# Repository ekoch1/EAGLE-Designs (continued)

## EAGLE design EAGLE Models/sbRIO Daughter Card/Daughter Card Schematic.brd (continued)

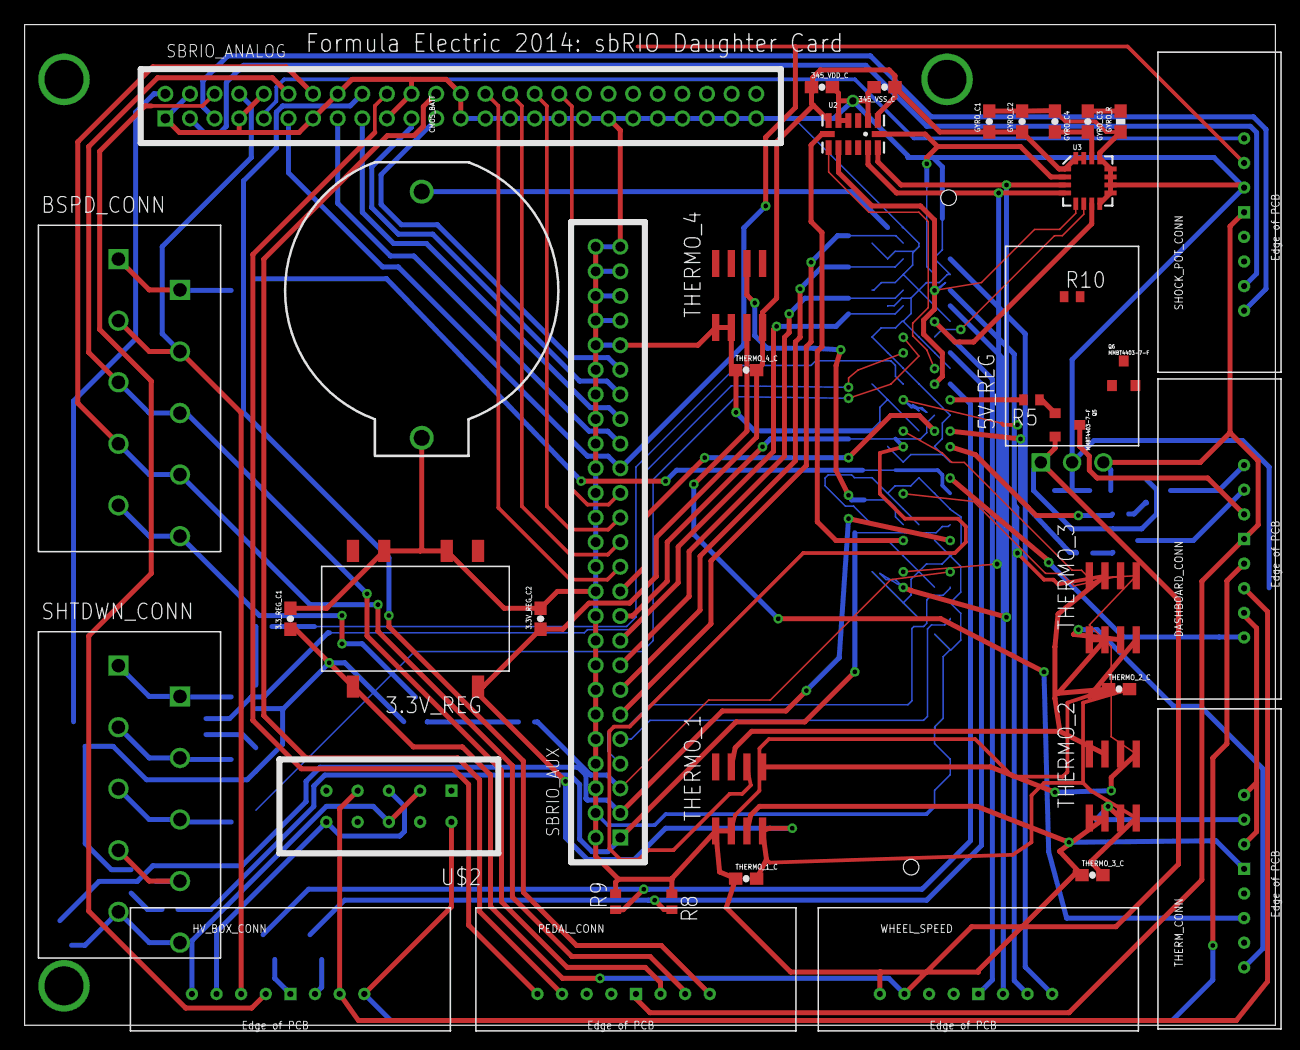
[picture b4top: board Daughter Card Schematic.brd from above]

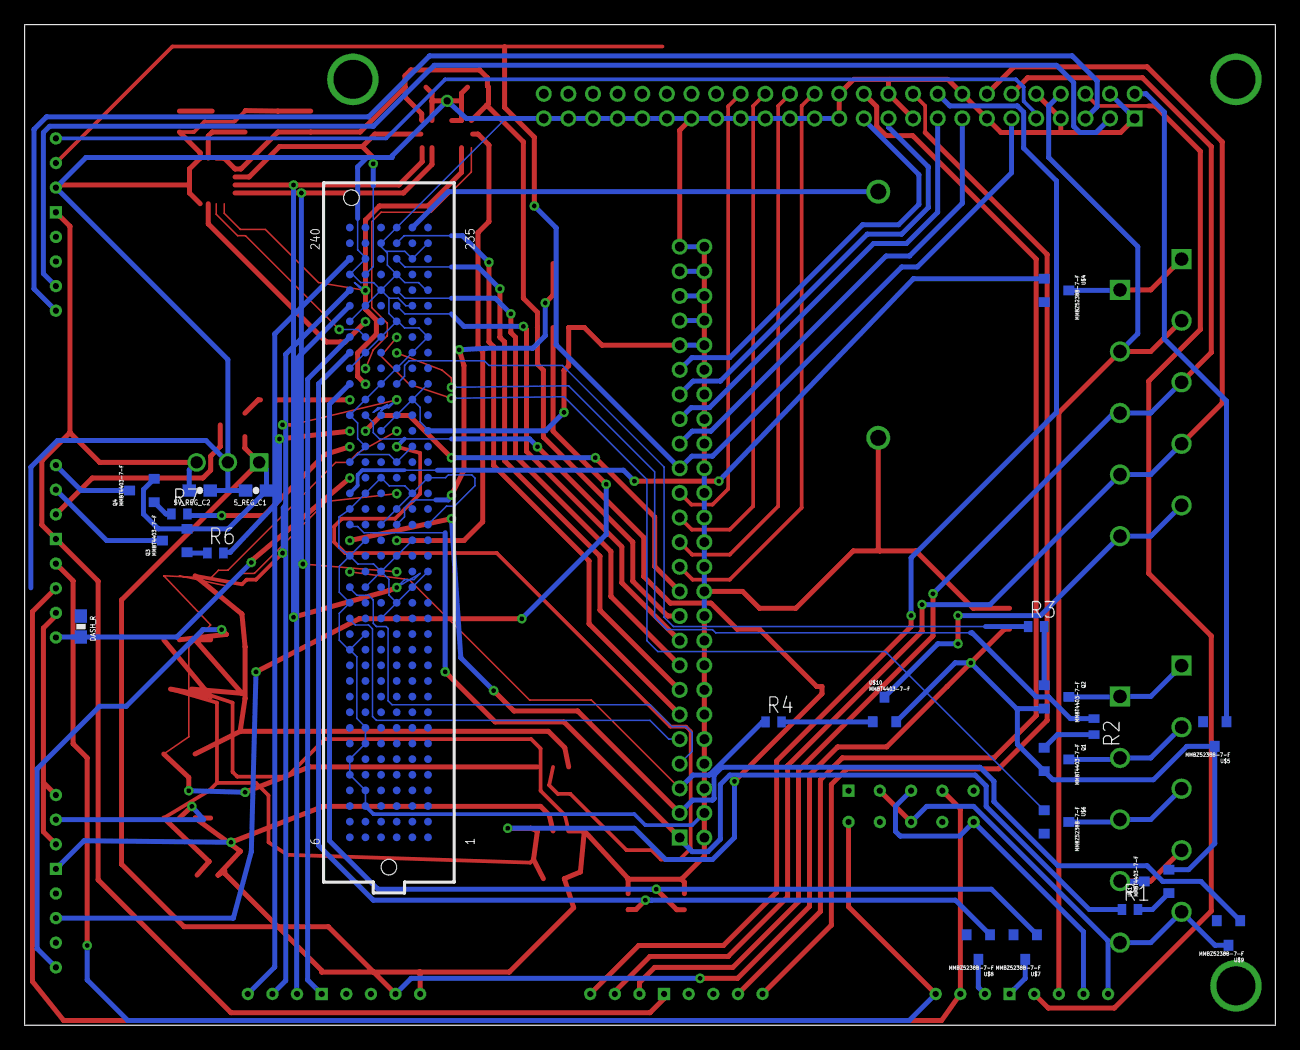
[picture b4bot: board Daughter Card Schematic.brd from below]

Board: 2 copper layers, 101.6 x 81.3 mm, 61 parts (22 on the bottom side), 95 nets.

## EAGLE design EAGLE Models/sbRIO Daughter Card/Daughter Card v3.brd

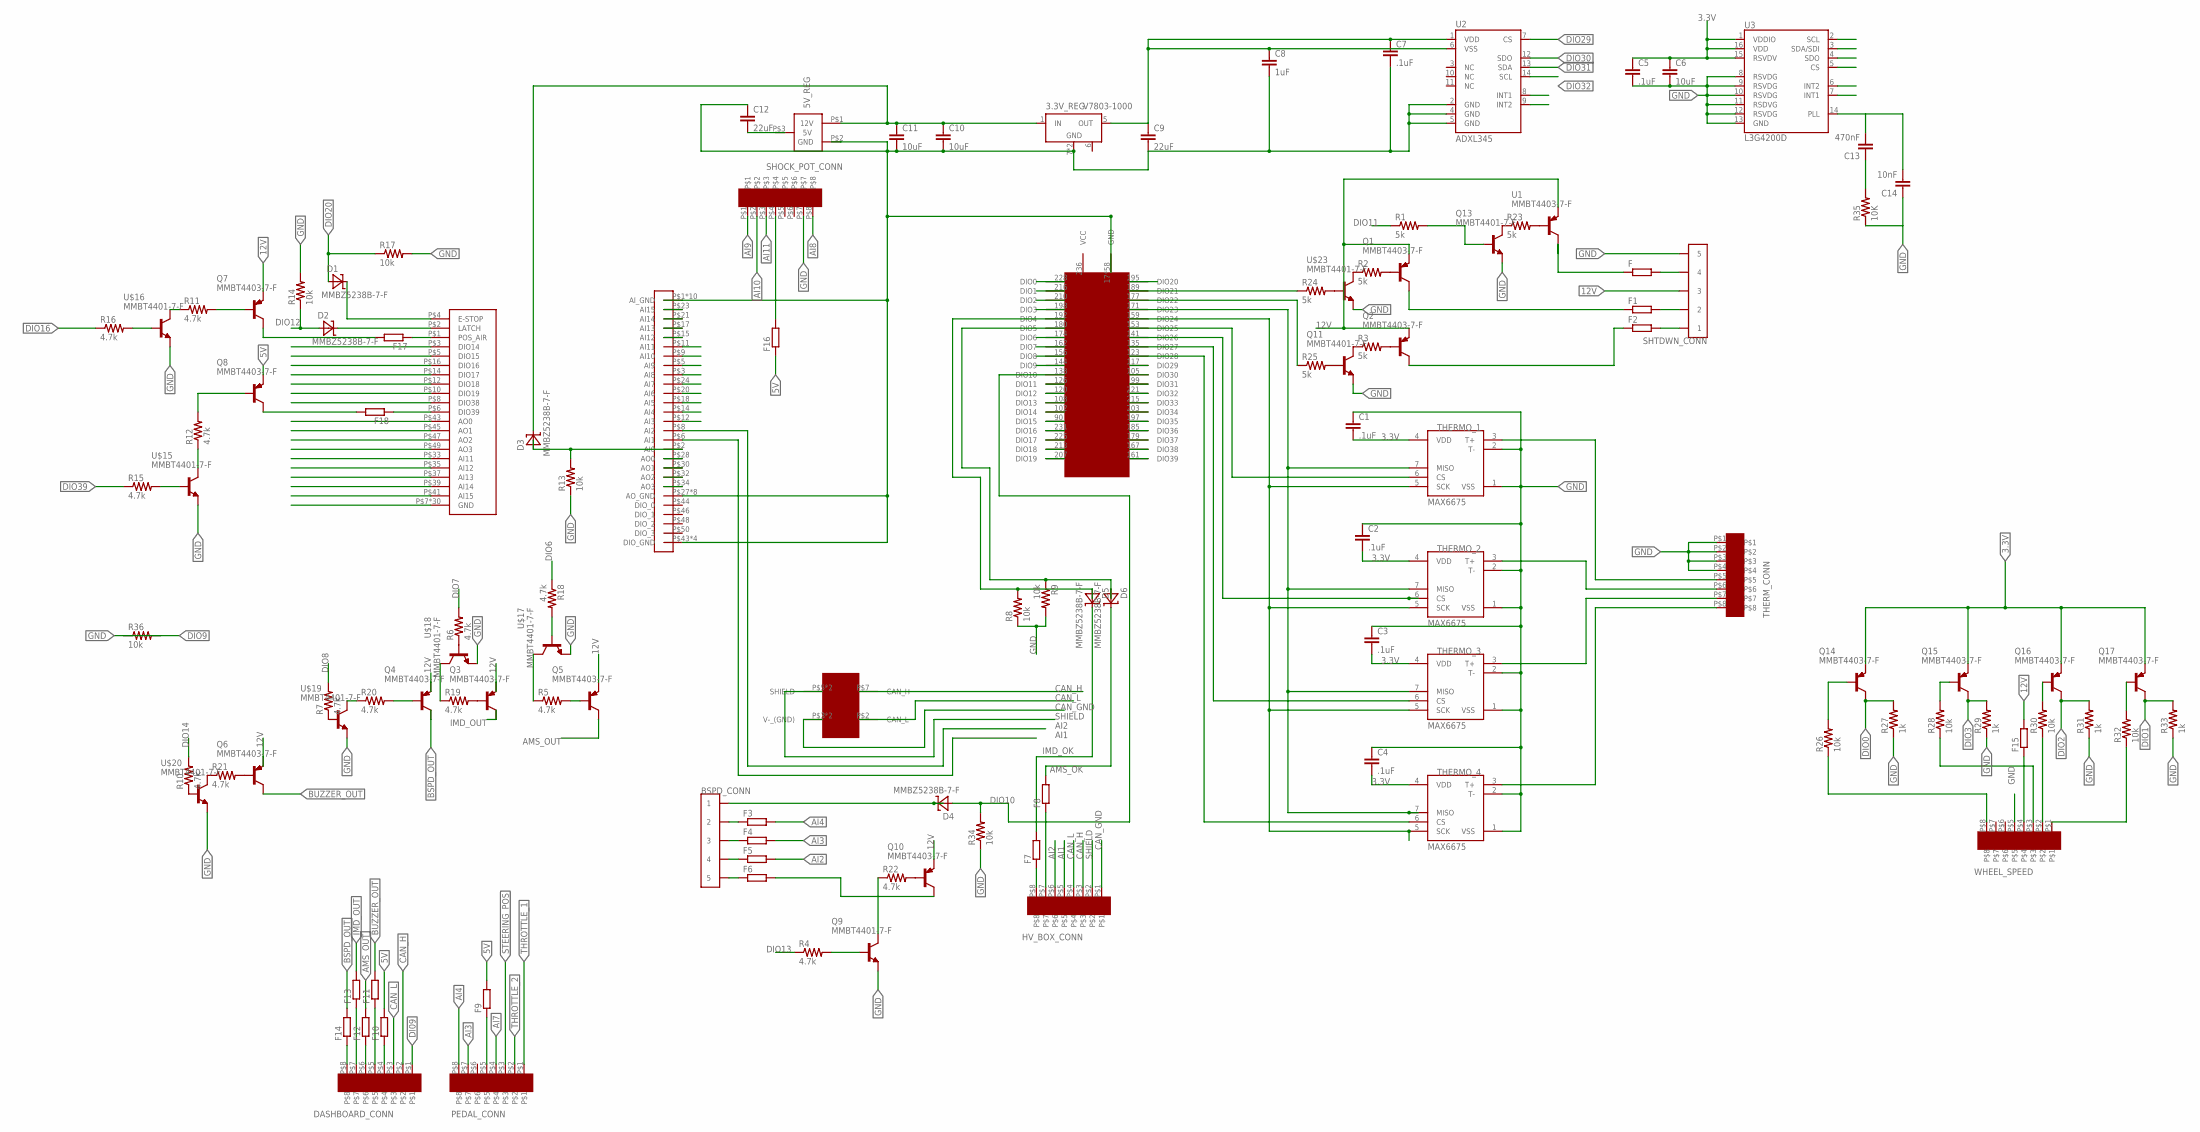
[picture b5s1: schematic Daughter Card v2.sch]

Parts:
3.3V_REG: V7803-1000; V78XX-1000
5V_REG: V78XX-1500; V78XX-1500R
BSPD_CONN: CONN_5; CONNECTOR_5
C1, C2, C3, C4, C5, C7: .1uF; 0603-CAP
C6, C10, C11: 10uF; 0603-CAP
C8: 1uF; 0603-CAP
C9, C12: 22uF; 0603-CAP
C13: 470nF; 0603-CAP
C14: 10nF; 0603-CAP
D1, D2, D3, D4, D5, D6: MMBZ5238B-7-F; SOT-23-3
DASHBOARD_CONN: EN3_PCB_8
F, F1, F2, F3, F4, F5, F6, F7, F8, F9, F10, F11, F12, F13, F14, F15, F16, F17, F18: R-EU_R0402; R0402
HV_BOX_CONN: EN3_PCB_8
PEDAL_CONN: EN3_PCB_8
Q1, Q2, Q3, Q4, Q5, Q6, Q7, Q8, Q10, Q14, Q15, Q16, Q17: MMBT4403-7-F; SOT-23-3
Q9, Q11, Q13: MMBT4401-7-F; SOT-23-3
R1, R2, R3, R23, R24, R25: 5k; R0402
R4, R5, R6, R7, R10, R11, R12, R15, R16, R18, R19, R20, R21, R22: 4.7k; R0402
R8, R9, R13, R14, R17, R26, R28, R30, R32, R34, R36: 10k; R0402
R27, R29, R31, R33: 1k; R0402
R35: 10K; 0603-RES
SBRIO_ANALOG: SBRIO_MIO; SBRIO_J502_J503
SBRIO_AUX: SBRIO_AUX; SBRIO_J502_J503
SHOCK_POT_CONN: EN3_PCB_8
SHTDWN_CONN: CONN_5; CONNECTOR_5
THERMO_1, THERMO_2, THERMO_3, THERMO_4: MAX6675; SO08
THERM_CONN: EN3_PCB_8
U1: MMBT4403-7-F; SOT-23-3
U2: ADXL345; LGA14
U3: L3G4200D; LGA16-4X4
U$2: SBRIO_W500; SBRIO_W
U$3: SBRIO_RMC; SEAM-40-XX.X-XX-06-X-A
U$15, U$16, U$17, U$18, U$19, U$20, U$23: MMBT4401-7-F; SOT-23-3
WHEEL_SPEED: EN3_PCB_8

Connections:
3.3V: 3.3V_REG.5 (OUT), C1.2, C2.2, C3.2, C4.2, C5.1, C6.1, C7.1, C8.1, C9.1, Q14.P$3 (E), Q15.P$3 (E), Q16.P$3 (E), Q17.P$3 (E), THERMO_1.4 (VDD), THERMO_2.4 (VDD), THERMO_3.4 (VDD), THERMO_4.4 (VDD), U2.1 (VDD), U2.6 (VSS), U3.1 (VDDIO), U3.15 (RSVDV), U3.16 (VDD)
AI1: HV_BOX_CONN.P$5, SBRIO_ANALOG.P$6 (AI1)
AI2: F5.2, HV_BOX_CONN.P$6, SBRIO_ANALOG.P$8 (AI2)
AI3: F4.2, PEDAL_CONN.P$7, SBRIO_ANALOG.P$12 (AI3)
AI4: F3.2, PEDAL_CONN.P$8, SBRIO_ANALOG.P$14 (AI4)
AI7: PEDAL_CONN.P$4, SBRIO_ANALOG.P$24 (AI7)
AI8: SBRIO_ANALOG.P$3 (AI8), SHOCK_POT_CONN.P$8
AI9: SBRIO_ANALOG.P$5 (AI9), SHOCK_POT_CONN.P$1
AI10: SBRIO_ANALOG.P$9 (AI10), SHOCK_POT_CONN.P$2
AI11: SBRIO_ANALOG.P$11 (AI11), SBRIO_AUX.P$33 (AI11), SHOCK_POT_CONN.P$3
AI12: SBRIO_ANALOG.P$15 (AI12), SBRIO_AUX.P$35 (AI12)
AI13: SBRIO_ANALOG.P$17 (AI13), SBRIO_AUX.P$37 (AI13)
AI15: SBRIO_ANALOG.P$23 (AI15), SBRIO_AUX.P$41 (AI15)
AMS_OK: D6.P$1 (C), F8.2
AMS_OUT: F12.2, Q5.P$1 (C)
AO0: SBRIO_ANALOG.P$28 (AO0), SBRIO_AUX.P$43 (AO0)
AO1: SBRIO_ANALOG.P$30 (AO1), SBRIO_AUX.P$45 (AO1)
AO2: SBRIO_ANALOG.P$32 (AO2), SBRIO_AUX.P$47 (AO2)
AO3: SBRIO_ANALOG.P$34 (AO3), SBRIO_AUX.P$49 (AO3)
BSPD_OUT: F14.2, Q4.P$1 (C)
BUZZER_OUT: F11.2, Q6.P$1 (C)
CAN_GND: HV_BOX_CONN.P$1, U$2.P$3 (V-_(GND)), U$2.P$6 (V-_(GND))
CAN_H: DASHBOARD_CONN.P$2, HV_BOX_CONN.P$3, U$2.P$7 (CAN_H)
CAN_L: DASHBOARD_CONN.P$3, HV_BOX_CONN.P$4, U$2.P$2 (CAN_L)
DI09: DASHBOARD_CONN.P$1
DIO0: Q14.P$1 (C), R27.2, U$3.228 (DIO0)
DIO1: Q17.P$1 (C), R33.2, U$3.216 (DIO1)
DIO2: Q16.P$1 (C), R31.2, U$3.210 (DIO2)
DIO3: Q15.P$1 (C), R29.2, U$3.198 (DIO3)
DIO6: R18.1, U$3.174 (DIO6)
DIO7: R6.2, U$3.162 (DIO7)
DIO8: R7.2, U$3.156 (DIO8)
DIO9: R36.2, U$3.144 (DIO9)
DIO10: D4.P$2 (A), R34.2, U$3.138 (DIO10)
DIO11: R1.1, U$3.126 (DIO11)
DIO12: D2.P$2 (A), R14.1, U$3.120 (DIO12)
DIO13: R4.1, U$3.108 (DIO13)
DIO14: R10.2, SBRIO_AUX.P$3 (DIO14), U$3.102 (DIO14)
DIO15: SBRIO_AUX.P$5 (DIO15), U$3.90 (DIO15)
DIO16: R16.1, SBRIO_AUX.P$16 (DIO16), U$3.231 (DIO16)
DIO17: SBRIO_AUX.P$14 (DIO17), U$3.225 (DIO17)
DIO18: SBRIO_AUX.P$12 (DIO18), U$3.213 (DIO18)
DIO19: SBRIO_AUX.P$10 (DIO19), U$3.207 (DIO19)
DIO20: D1.P$2 (A), R17.1, U$3.195 (DIO20)
DIO29: U2.7 (CS), U$3.117 (DIO29)
DIO30: U2.12 (SDO), U3.4 (SDO), U$3.105 (DIO30)
DIO31: U2.13 (SDA), U3.3 (SDA/SDI), U$3.99 (DIO31)
DIO32: U2.14 (SCL), U3.2 (SCL), U$3.221 (DIO32)
DIO33: U3.5 (CS), U$3.215 (DIO33)
DIO34: U3.7 (INT1), U$3.203 (DIO34)
DIO35: U3.6 (INT2), U$3.197 (DIO35)
DIO36: U2.8 (INT1), U$3.185 (DIO36)
DIO37: U2.9 (INT2), U$3.179 (DIO37)
DIO38: SBRIO_AUX.P$8 (DIO38), U$3.167 (DIO38)
DIO39: R15.1, U$3.161 (DIO39)
GND: 3.3V_REG.7 (GND), 3.3V_REG.9 (GND), 5V_REG.P$2 (GND), C1.1, C2.1, C3.1, C4.1, C5.2, C6.2, C7.2, C8.2, C9.2, C10.2, C11.2, C12.1, C14.1, Q9.P$3 (E), Q11.P$3 (E), Q13.P$3 (E), R8.1, R9.2, R13.1, R14.2, R17.2, R27.1, R29.1, R31.1, R33.1, R34.1, R35.1, R36.1, SBRIO_ANALOG.P$1 (AI_GND), SBRIO_ANALOG.P$4 (AI_GND), SBRIO_ANALOG.P$7 (AI_GND), SBRIO_ANALOG.P$10 (AI_GND), SBRIO_ANALOG.P$13 (AI_GND), SBRIO_ANALOG.P$16 (AI_GND), SBRIO_ANALOG.P$19 (AI_GND), SBRIO_ANALOG.P$22 (AI_GND), SBRIO_ANALOG.P$25 (AI_GND), SBRIO_ANALOG.P$26 (AI_GND), SBRIO_ANALOG.P$27 (AO_GND), SBRIO_ANALOG.P$29 (AO_GND), SBRIO_ANALOG.P$31 (AO_GND), SBRIO_ANALOG.P$33 (AO_GND), SBRIO_ANALOG.P$35 (AO_GND), SBRIO_ANALOG.P$37 (AO_GND), SBRIO_ANALOG.P$39 (AO_GND), SBRIO_ANALOG.P$41 (AO_GND), SBRIO_ANALOG.P$43 (DIO_GND), SBRIO_ANALOG.P$45 (DIO_GND), SBRIO_ANALOG.P$47 (DIO_GND), SBRIO_ANALOG.P$49 (DIO_GND), SBRIO_AUX.P$7 (GND), SBRIO_AUX.P$9 (GND), SBRIO_AUX.P$11 (GND), SBRIO_AUX.P$13 (GND), SBRIO_AUX.P$15 (GND), SBRIO_AUX.P$17 (GND), SBRIO_AUX.P$18 (GND), SBRIO_AUX.P$19 (GND), SBRIO_AUX.P$20 (GND), SBRIO_AUX.P$21 (GND), SBRIO_AUX.P$22 (GND), SBRIO_AUX.P$23 (GND), SBRIO_AUX.P$24 (GND), SBRIO_AUX.P$25 (GND), SBRIO_AUX.P$26 (GND), SBRIO_AUX.P$27 (GND), SBRIO_AUX.P$28 (GND), SBRIO_AUX.P$29 (GND), SBRIO_AUX.P$30 (GND), SBRIO_AUX.P$31 (GND), SBRIO_AUX.P$32 (GND), SBRIO_AUX.P$34 (GND), SBRIO_AUX.P$36 (GND), SBRIO_AUX.P$38 (GND), SBRIO_AUX.P$40 (GND), SBRIO_AUX.P$42 (GND), SBRIO_AUX.P$44 (GND), SBRIO_AUX.P$46 (GND), SBRIO_AUX.P$48 (GND), SBRIO_AUX.P$50 (GND), SHOCK_POT_CONN.P$7, SHTDWN_CONN.9 (5), SHTDWN_CONN.10 (5), THERMO_1.1 (VSS), THERMO_1.2 (T-), THERMO_2.1 (VSS), THERMO_2.2 (T-), THERMO_3.1 (VSS), THERMO_3.2 (T-), THERMO_4.1 (VSS), THERMO_4.2 (T-), THERM_CONN.P$1, THERM_CONN.P$2, THERM_CONN.P$3, THERM_CONN.P$4, U2.2 (GND), U2.4 (GND), U2.5 (GND), U3.8 (RSVDG), U3.9 (RSVDG), U3.10 (RSVDG), U3.11 (RSDVG), U3.12 (RSVDG), U3.13 (GND), U$3.17 (GND), U$3.237 (GND), U$15.P$3 (E), U$16.P$3 (E), U$17.P$3 (E), U$18.P$3 (E), U$19.P$3 (E), U$20.P$3 (E), U$23.P$3 (E), WHEEL_SPEED.P$5
IMD_OK: D5.P$1 (C), F7.2
IMD_OUT: F13.2, Q3.P$1 (C)
unnamed: D2.P$1 (C), SBRIO_AUX.P$2 (LATCH)
unnamed: D1.P$1 (C), SBRIO_AUX.P$4 (E-STOP)
unnamed: R32.1, WHEEL_SPEED.P$1
unnamed: D3.P$2 (A), R13.2, SBRIO_ANALOG.P$2 (AI0)
unnamed: Q6.P$2 (B), R21.2
unnamed: Q16.P$2 (B), R30.2
unnamed: F1.1, Q1.P$1 (C)
unnamed: F2.1, Q2.P$1 (C)
unnamed: R28.1, WHEEL_SPEED.P$3
unnamed: R26.1, WHEEL_SPEED.P$8
unnamed: R24.1, U$3.189 (DIO21)
unnamed: R25.1, U$3.177 (DIO22)
unnamed: F8.1, HV_BOX_CONN.P$7
unnamed: F7.1, HV_BOX_CONN.P$8
unnamed: D5.P$2 (A), R8.2, U$3.192 (DIO4)
unnamed: D6.P$2 (A), R9.1, U$3.180 (DIO5)
unnamed: THERMO_1.7 (MISO), THERMO_2.7 (MISO), THERMO_3.7 (MISO), THERMO_4.7 (MISO), U$3.171 (DIO23)
unnamed: THERMO_1.5 (SCK), THERMO_2.5 (SCK), THERMO_3.5 (SCK), THERMO_4.5 (SCK), U$3.159 (DIO24)
unnamed: F16.2, SHOCK_POT_CONN.P$4
unnamed: F15.1, WHEEL_SPEED.P$4
unnamed: F9.1, PEDAL_CONN.P$5
unnamed: DASHBOARD_CONN.P$4, F10.1
unnamed: DASHBOARD_CONN.P$5, F11.1
unnamed: THERMO_1.6 (CS), U$3.153 (DIO25)
unnamed: THERMO_2.6 (CS), U$3.141 (DIO26)
unnamed: THERMO_3.6 (CS), U$3.135 (DIO27)
unnamed: THERMO_4.6 (CS), U$3.123 (DIO28)
unnamed: THERMO_1.3 (T+), THERM_CONN.P$5
unnamed: THERMO_2.3 (T+), THERM_CONN.P$6
unnamed: THERMO_3.3 (T+), THERM_CONN.P$7
unnamed: THERMO_4.3 (T+), THERM_CONN.P$8
unnamed: DASHBOARD_CONN.P$6, F12.1
unnamed: DASHBOARD_CONN.P$7, F13.1
unnamed: DASHBOARD_CONN.P$8, F14.1
unnamed: F.2, SHTDWN_CONN.7 (4), SHTDWN_CONN.8 (4)
unnamed: C13.2, C14.2, U3.14 (PLL)
unnamed: C13.1, R35.2
unnamed: F1.2, SHTDWN_CONN.3 (2), SHTDWN_CONN.4 (2)
unnamed: F2.2, SHTDWN_CONN.1, SHTDWN_CONN.2 (1)
unnamed: BSPD_CONN.9 (5), BSPD_CONN.10 (5), F6.1
unnamed: BSPD_CONN.1, BSPD_CONN.2 (1), D4.P$1 (C)
unnamed: BSPD_CONN.7 (4), BSPD_CONN.8 (4), F5.1
unnamed: F.1, U1.P$1 (C)
unnamed: F6.2, Q10.P$1 (C)
unnamed: R23.2, U1.P$2 (B)
unnamed: Q1.P$2 (B), R2.2
unnamed: Q2.P$2 (B), R3.2
unnamed: Q10.P$2 (B), R22.2
unnamed: Q5.P$2 (B), R5.2
unnamed: Q3.P$2 (B), R19.2
unnamed: BSPD_CONN.5 (3), BSPD_CONN.6 (3), F4.1
unnamed: BSPD_CONN.3 (2), BSPD_CONN.4 (2), F3.1
unnamed: Q7.P$2 (B), R11.2
unnamed: F17.1, SBRIO_AUX.P$1 (POS_AIR)
unnamed: F17.2, Q7.P$1 (C)
unnamed: F18.2, Q8.P$1 (C)
unnamed: Q8.P$2 (B), R12.2
unnamed: F18.1, SBRIO_AUX.P$6 (DIO39)
unnamed: R15.2, U$15.P$2 (B)
unnamed: R12.1, U$15.P$1 (C)
unnamed: R16.2, U$16.P$2 (B)
unnamed: R11.1, U$16.P$1 (C)
unnamed: R5.1, U$17.P$1 (C)
unnamed: R18.2, U$17.P$2 (B)
unnamed: R19.1, U$18.P$1 (C)
unnamed: R6.1, U$18.P$2 (B)
unnamed: Q4.P$2 (B), R20.2
unnamed: R20.1, U$19.P$1 (C)
unnamed: R7.1, U$19.P$2 (B)
unnamed: R21.1, U$20.P$1 (C)
unnamed: R10.1, U$20.P$2 (B)
unnamed: Q9.P$1 (C), R22.1
unnamed: Q9.P$2 (B), R4.2
unnamed: Q13.P$1 (C), R23.1
unnamed: Q13.P$2 (B), R1.2
unnamed: R2.1, U$23.P$1 (C)
unnamed: Q11.P$1 (C), R3.1
unnamed: R24.2, U$23.P$2 (B)
unnamed: Q11.P$2 (B), R25.2
unnamed: Q14.P$2 (B), R26.2
unnamed: Q15.P$2 (B), R28.2
unnamed: R30.1, WHEEL_SPEED.P$2
unnamed: Q17.P$2 (B), R32.2
SHIELD: HV_BOX_CONN.P$2, U$2.P$5 (SHIELD), U$2.P$10 (SHIELD)
STEERING_POS: PEDAL_CONN.P$3, SBRIO_ANALOG.P$21 (AI14), SBRIO_AUX.P$39 (AI14)
THROTTLE_1: PEDAL_CONN.P$1, SBRIO_ANALOG.P$18 (AI5)
THROTTLE_2: PEDAL_CONN.P$2, SBRIO_ANALOG.P$20 (AI6)
VCC: U$3.236 (VCC)

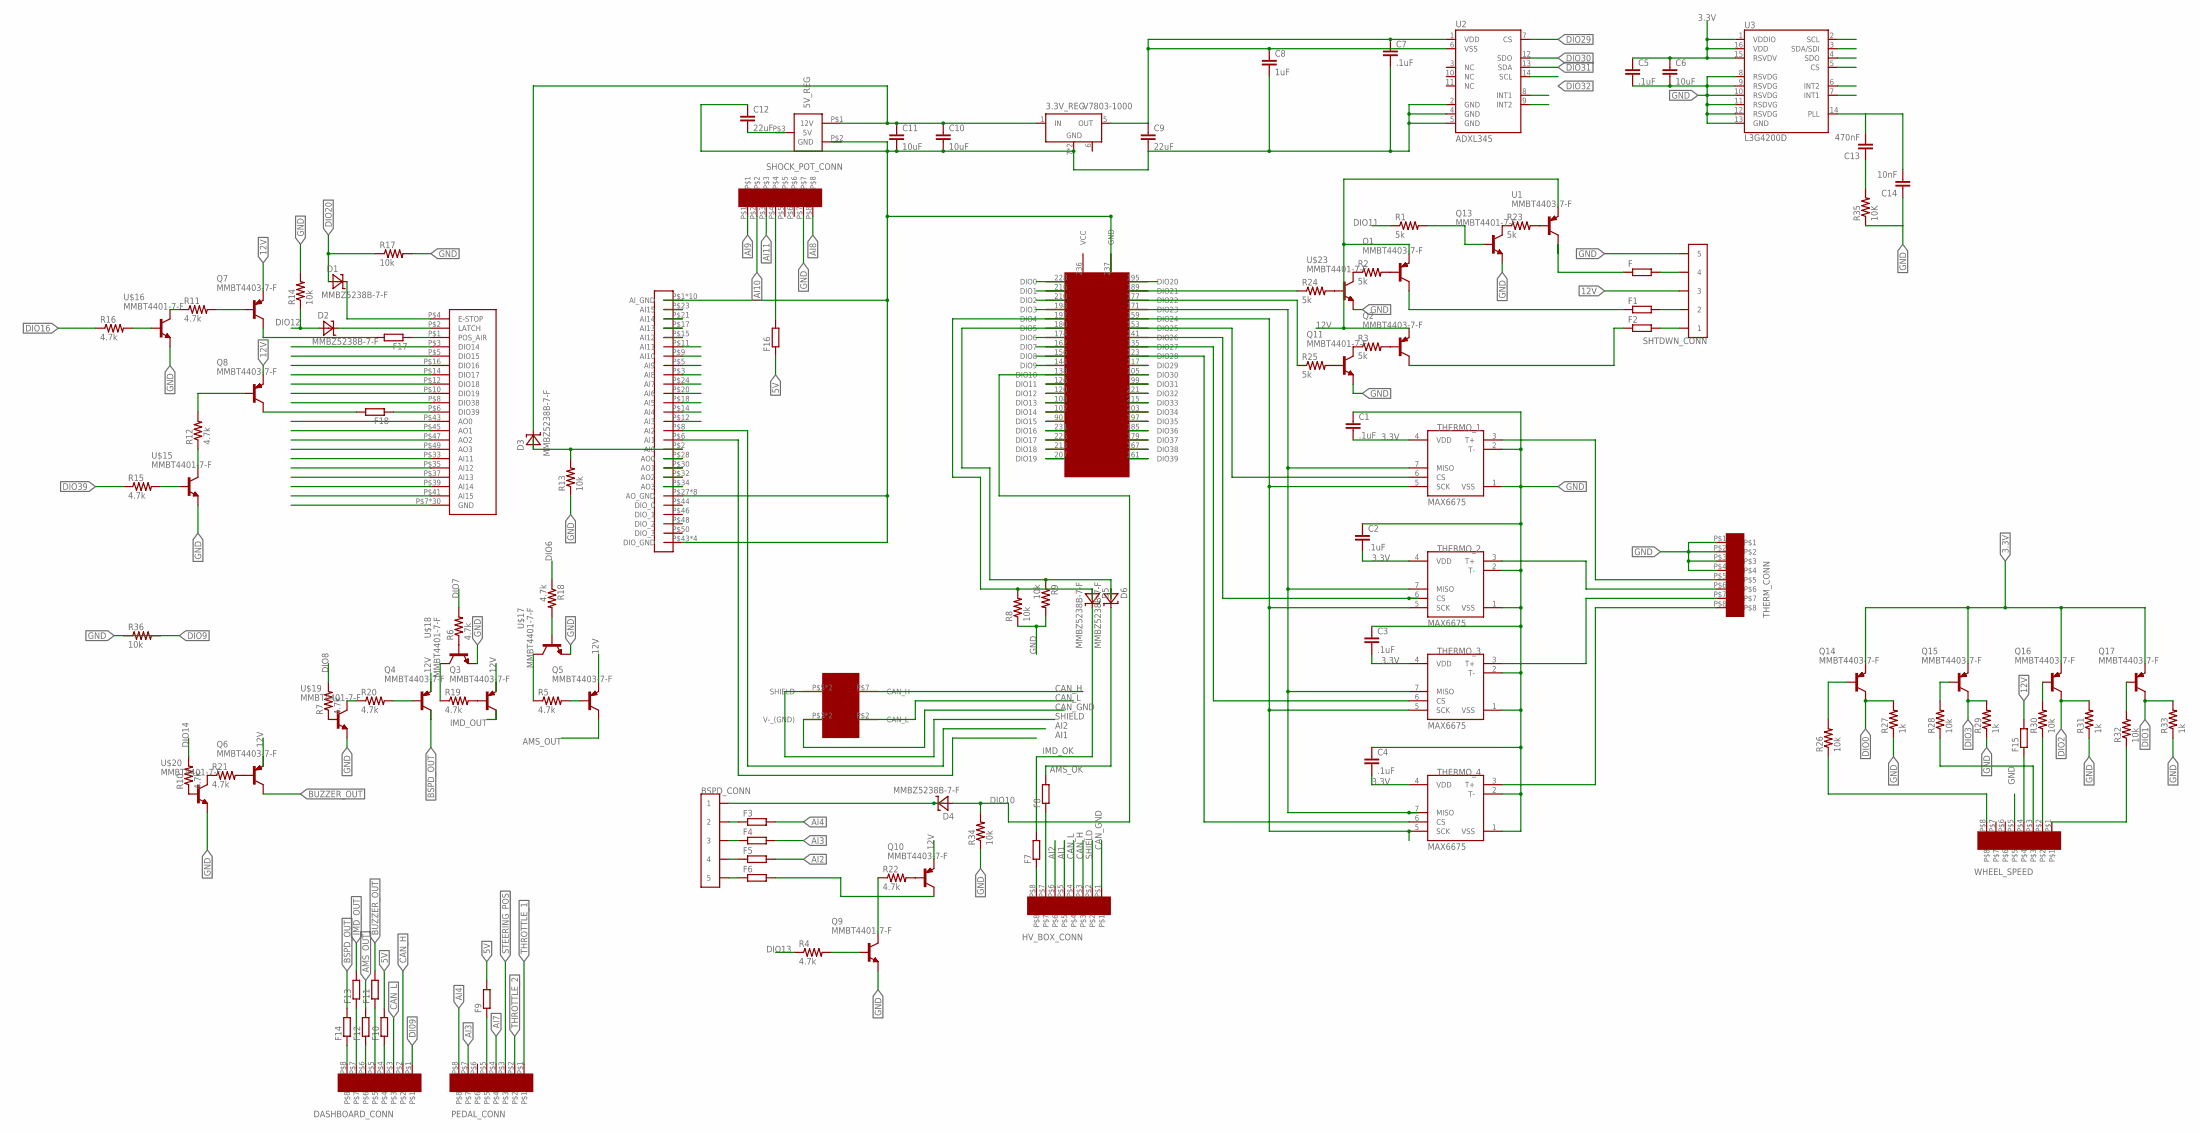
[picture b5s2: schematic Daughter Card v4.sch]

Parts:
3.3V_REG: V7803-1000; V78XX-1000
5V_REG: V78XX-1500; V78XX-1500R
BSPD_CONN: CONN_5; CONNECTOR_5
C1, C2, C3, C4, C5, C7: .1uF; 0603-CAP
C6, C10, C11: 10uF; 0603-CAP
C8: 1uF; 0603-CAP
C9, C12: 22uF; 0603-CAP
C13: 470nF; 0603-CAP
C14: 10nF; 0603-CAP
D1, D2, D3, D4, D5, D6: MMBZ5238B-7-F; SOT-23-3
DASHBOARD_CONN: EN3_PCB_8
F, F1, F2, F3, F4, F5, F6, F7, F8, F9, F10, F11, F12, F13, F14, F15, F16, F17, F18: R-EU_R0402; R0402
HV_BOX_CONN: EN3_PCB_8
PEDAL_CONN: EN3_PCB_8
Q1, Q2, Q3, Q4, Q5, Q6, Q7, Q8, Q10, Q14, Q15, Q16, Q17: MMBT4403-7-F; SOT-23-3
Q9, Q11, Q13: MMBT4401-7-F; SOT-23-3
R1, R2, R3, R23, R24, R25: 5k; R0402
R4, R5, R6, R7, R10, R11, R12, R15, R16, R18, R19, R20, R21, R22: 4.7k; R0402
R8, R9, R13, R14, R17, R26, R28, R30, R32, R34, R36: 10k; R0402
R27, R29, R31, R33: 1k; R0402
R35: 10K; 0603-RES
SBRIO_ANALOG: SBRIO_MIO; SBRIO_J502_J503
SBRIO_AUX: SBRIO_AUX; SBRIO_J502_J503
SHOCK_POT_CONN: EN3_PCB_8
SHTDWN_CONN: CONN_5; CONNECTOR_5
THERMO_1, THERMO_2, THERMO_3, THERMO_4: MAX6675; SO08
THERM_CONN: EN3_PCB_8
U1: MMBT4403-7-F; SOT-23-3
U2: ADXL345; LGA14
U3: L3G4200D; LGA16-4X4
U$2: SBRIO_W500; SBRIO_W
U$3: SBRIO_RMC; SEAM-40-XX.X-XX-06-X-A
U$15, U$16, U$17, U$18, U$19, U$20, U$23: MMBT4401-7-F; SOT-23-3
WHEEL_SPEED: EN3_PCB_8

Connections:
3.3V: 3.3V_REG.5 (OUT), C1.2, C2.2, C3.2, C4.2, C5.1, C6.1, C7.1, C8.1, C9.1, Q14.P$3 (E), Q15.P$3 (E), Q16.P$3 (E), Q17.P$3 (E), THERMO_1.4 (VDD), THERMO_2.4 (VDD), THERMO_3.4 (VDD), THERMO_4.4 (VDD), U2.1 (VDD), U2.6 (VSS), U3.1 (VDDIO), U3.15 (RSVDV), U3.16 (VDD)
AI1: HV_BOX_CONN.P$5, SBRIO_ANALOG.P$6 (AI1)
AI2: F5.2, HV_BOX_CONN.P$6, SBRIO_ANALOG.P$8 (AI2)
AI3: F4.2, PEDAL_CONN.P$7, SBRIO_ANALOG.P$12 (AI3)
AI4: F3.2, PEDAL_CONN.P$8, SBRIO_ANALOG.P$14 (AI4)
AI7: PEDAL_CONN.P$4, SBRIO_ANALOG.P$24 (AI7)
AI8: SBRIO_ANALOG.P$3 (AI8), SHOCK_POT_CONN.P$8
AI9: SBRIO_ANALOG.P$5 (AI9), SHOCK_POT_CONN.P$1
AI10: SBRIO_ANALOG.P$9 (AI10), SHOCK_POT_CONN.P$2
AI11: SBRIO_ANALOG.P$11 (AI11), SBRIO_AUX.P$33 (AI11), SHOCK_POT_CONN.P$3
AI12: SBRIO_ANALOG.P$15 (AI12), SBRIO_AUX.P$35 (AI12)
AI13: SBRIO_ANALOG.P$17 (AI13), SBRIO_AUX.P$37 (AI13)
AI15: SBRIO_ANALOG.P$23 (AI15), SBRIO_AUX.P$41 (AI15)
AMS_OK: D6.P$1 (C), F8.2
AMS_OUT: F12.2, Q5.P$1 (C)
AO0: SBRIO_ANALOG.P$28 (AO0), SBRIO_AUX.P$43 (AO0)
AO1: SBRIO_ANALOG.P$30 (AO1), SBRIO_AUX.P$45 (AO1)
AO2: SBRIO_ANALOG.P$32 (AO2), SBRIO_AUX.P$47 (AO2)
AO3: SBRIO_ANALOG.P$34 (AO3), SBRIO_AUX.P$49 (AO3)
BSPD_OUT: F14.2, Q4.P$1 (C)
BUZZER_OUT: F11.2, Q6.P$1 (C)
CAN_GND: HV_BOX_CONN.P$1, U$2.P$3 (V-_(GND)), U$2.P$6 (V-_(GND))
CAN_H: DASHBOARD_CONN.P$2, HV_BOX_CONN.P$3, U$2.P$7 (CAN_H)
CAN_L: DASHBOARD_CONN.P$3, HV_BOX_CONN.P$4, U$2.P$2 (CAN_L)
DI09: DASHBOARD_CONN.P$1
DIO0: Q14.P$1 (C), R27.2, U$3.228 (DIO0)
DIO1: Q17.P$1 (C), R33.2, U$3.216 (DIO1)
DIO2: Q16.P$1 (C), R31.2, U$3.210 (DIO2)
DIO3: Q15.P$1 (C), R29.2, U$3.198 (DIO3)
DIO6: R18.1, U$3.174 (DIO6)
DIO7: R6.2, U$3.162 (DIO7)
DIO8: R7.2, U$3.156 (DIO8)
DIO9: R36.2, U$3.144 (DIO9)
DIO10: D4.P$2 (A), R34.2, U$3.138 (DIO10)
DIO11: R1.1, U$3.126 (DIO11)
DIO12: D2.P$2 (A), R14.1, U$3.120 (DIO12)
DIO13: R4.1, U$3.108 (DIO13)
DIO14: R10.2, SBRIO_AUX.P$3 (DIO14), U$3.102 (DIO14)
DIO15: SBRIO_AUX.P$5 (DIO15), U$3.90 (DIO15)
DIO16: R16.1, SBRIO_AUX.P$16 (DIO16), U$3.231 (DIO16)
DIO17: SBRIO_AUX.P$14 (DIO17), U$3.225 (DIO17)
DIO18: SBRIO_AUX.P$12 (DIO18), U$3.213 (DIO18)
DIO19: SBRIO_AUX.P$10 (DIO19), U$3.207 (DIO19)
DIO20: D1.P$2 (A), R17.1, U$3.195 (DIO20)
DIO29: U2.7 (CS), U$3.117 (DIO29)
DIO30: U2.12 (SDO), U3.4 (SDO), U$3.105 (DIO30)
DIO31: U2.13 (SDA), U3.3 (SDA/SDI), U$3.99 (DIO31)
DIO32: U2.14 (SCL), U3.2 (SCL), U$3.221 (DIO32)
DIO33: U3.5 (CS), U$3.215 (DIO33)
DIO34: U3.7 (INT1), U$3.203 (DIO34)
DIO35: U3.6 (INT2), U$3.197 (DIO35)
DIO36: U2.8 (INT1), U$3.185 (DIO36)
DIO37: U2.9 (INT2), U$3.179 (DIO37)
DIO38: SBRIO_AUX.P$8 (DIO38), U$3.167 (DIO38)
DIO39: R15.1, U$3.161 (DIO39)
GND: 3.3V_REG.7 (GND), 3.3V_REG.9 (GND), 5V_REG.P$2 (GND), C1.1, C2.1, C3.1, C4.1, C5.2, C6.2, C7.2, C8.2, C9.2, C10.2, C11.2, C12.1, C14.1, Q9.P$3 (E), Q11.P$3 (E), Q13.P$3 (E), R8.1, R9.2, R13.1, R14.2, R17.2, R27.1, R29.1, R31.1, R33.1, R34.1, R35.1, R36.1, SBRIO_ANALOG.P$1 (AI_GND), SBRIO_ANALOG.P$4 (AI_GND), SBRIO_ANALOG.P$7 (AI_GND), SBRIO_ANALOG.P$10 (AI_GND), SBRIO_ANALOG.P$13 (AI_GND), SBRIO_ANALOG.P$16 (AI_GND), SBRIO_ANALOG.P$19 (AI_GND), SBRIO_ANALOG.P$22 (AI_GND), SBRIO_ANALOG.P$25 (AI_GND), SBRIO_ANALOG.P$26 (AI_GND), SBRIO_ANALOG.P$27 (AO_GND), SBRIO_ANALOG.P$29 (AO_GND), SBRIO_ANALOG.P$31 (AO_GND), SBRIO_ANALOG.P$33 (AO_GND), SBRIO_ANALOG.P$35 (AO_GND), SBRIO_ANALOG.P$37 (AO_GND), SBRIO_ANALOG.P$39 (AO_GND), SBRIO_ANALOG.P$41 (AO_GND), SBRIO_ANALOG.P$43 (DIO_GND), SBRIO_ANALOG.P$45 (DIO_GND), SBRIO_ANALOG.P$47 (DIO_GND), SBRIO_ANALOG.P$49 (DIO_GND), SBRIO_AUX.P$7 (GND), SBRIO_AUX.P$9 (GND), SBRIO_AUX.P$11 (GND), SBRIO_AUX.P$13 (GND), SBRIO_AUX.P$15 (GND), SBRIO_AUX.P$17 (GND), SBRIO_AUX.P$18 (GND), SBRIO_AUX.P$19 (GND), SBRIO_AUX.P$20 (GND), SBRIO_AUX.P$21 (GND), SBRIO_AUX.P$22 (GND), SBRIO_AUX.P$23 (GND), SBRIO_AUX.P$24 (GND), SBRIO_AUX.P$25 (GND), SBRIO_AUX.P$26 (GND), SBRIO_AUX.P$27 (GND), SBRIO_AUX.P$28 (GND), SBRIO_AUX.P$29 (GND), SBRIO_AUX.P$30 (GND), SBRIO_AUX.P$31 (GND), SBRIO_AUX.P$32 (GND), SBRIO_AUX.P$34 (GND), SBRIO_AUX.P$36 (GND), SBRIO_AUX.P$38 (GND), SBRIO_AUX.P$40 (GND), SBRIO_AUX.P$42 (GND), SBRIO_AUX.P$44 (GND), SBRIO_AUX.P$46 (GND), SBRIO_AUX.P$48 (GND), SBRIO_AUX.P$50 (GND), SHOCK_POT_CONN.P$7, SHTDWN_CONN.9 (5), SHTDWN_CONN.10 (5), THERMO_1.1 (VSS), THERMO_1.2 (T-), THERMO_2.1 (VSS), THERMO_2.2 (T-), THERMO_3.1 (VSS), THERMO_3.2 (T-), THERMO_4.1 (VSS), THERMO_4.2 (T-), THERM_CONN.P$1, THERM_CONN.P$2, THERM_CONN.P$3, THERM_CONN.P$4, U2.2 (GND), U2.4 (GND), U2.5 (GND), U3.8 (RSVDG), U3.9 (RSVDG), U3.10 (RSVDG), U3.11 (RSDVG), U3.12 (RSVDG), U3.13 (GND), U$3.237 (GND), U$15.P$3 (E), U$16.P$3 (E), U$17.P$3 (E), U$18.P$3 (E), U$19.P$3 (E), U$20.P$3 (E), U$23.P$3 (E), WHEEL_SPEED.P$5; also elsewhere on the board
IMD_OK: D5.P$1 (C), F7.2
IMD_OUT: F13.2, Q3.P$1 (C)
unnamed: D2.P$1 (C), SBRIO_AUX.P$2 (LATCH)
unnamed: D1.P$1 (C), SBRIO_AUX.P$4 (E-STOP)
unnamed: R32.1, WHEEL_SPEED.P$1
unnamed: D3.P$2 (A), R13.2, SBRIO_ANALOG.P$2 (AI0)
unnamed: Q6.P$2 (B), R21.2
unnamed: Q16.P$2 (B), R30.2
unnamed: F1.1, Q1.P$1 (C)
unnamed: F2.1, Q2.P$1 (C)
unnamed: R28.1, WHEEL_SPEED.P$3
unnamed: R26.1, WHEEL_SPEED.P$8
unnamed: R24.1, U$3.189 (DIO21)
unnamed: R25.1, U$3.177 (DIO22)
unnamed: F8.1, HV_BOX_CONN.P$7
unnamed: F7.1, HV_BOX_CONN.P$8
unnamed: D5.P$2 (A), R8.2, U$3.192 (DIO4)
unnamed: D6.P$2 (A), R9.1, U$3.180 (DIO5)
unnamed: THERMO_1.7 (MISO), THERMO_2.7 (MISO), THERMO_3.7 (MISO), THERMO_4.7 (MISO), U$3.171 (DIO23)
unnamed: THERMO_1.5 (SCK), THERMO_2.5 (SCK), THERMO_3.5 (SCK), THERMO_4.5 (SCK), U$3.159 (DIO24)
unnamed: F16.2, SHOCK_POT_CONN.P$4
unnamed: F15.1, WHEEL_SPEED.P$4
unnamed: F9.1, PEDAL_CONN.P$5
unnamed: DASHBOARD_CONN.P$4, F10.1
unnamed: DASHBOARD_CONN.P$5, F11.1
unnamed: THERMO_1.6 (CS), U$3.153 (DIO25)
unnamed: THERMO_2.6 (CS), U$3.141 (DIO26)
unnamed: THERMO_3.6 (CS), U$3.135 (DIO27)
unnamed: THERMO_4.6 (CS), U$3.123 (DIO28)
unnamed: THERMO_1.3 (T+), THERM_CONN.P$5
unnamed: THERMO_2.3 (T+), THERM_CONN.P$6
unnamed: THERMO_3.3 (T+), THERM_CONN.P$7
unnamed: THERMO_4.3 (T+), THERM_CONN.P$8
unnamed: DASHBOARD_CONN.P$6, F12.1
unnamed: DASHBOARD_CONN.P$7, F13.1
unnamed: DASHBOARD_CONN.P$8, F14.1
unnamed: F.2, SHTDWN_CONN.7 (4), SHTDWN_CONN.8 (4)
unnamed: C13.2, C14.2, U3.14 (PLL)
unnamed: C13.1, R35.2
unnamed: F1.2, SHTDWN_CONN.3 (2), SHTDWN_CONN.4 (2)
unnamed: F2.2, SHTDWN_CONN.1, SHTDWN_CONN.2 (1)
unnamed: BSPD_CONN.9 (5), BSPD_CONN.10 (5), F6.1
unnamed: BSPD_CONN.1, BSPD_CONN.2 (1), D4.P$1 (C)
unnamed: BSPD_CONN.7 (4), BSPD_CONN.8 (4), F5.1
unnamed: F.1, U1.P$1 (C)
unnamed: F6.2, Q10.P$1 (C)
unnamed: R23.2, U1.P$2 (B)
unnamed: Q1.P$2 (B), R2.2
unnamed: Q2.P$2 (B), R3.2
unnamed: Q10.P$2 (B), R22.2
unnamed: Q5.P$2 (B), R5.2
unnamed: Q3.P$2 (B), R19.2
unnamed: BSPD_CONN.5 (3), BSPD_CONN.6 (3), F4.1
unnamed: BSPD_CONN.3 (2), BSPD_CONN.4 (2), F3.1
unnamed: Q7.P$2 (B), R11.2
unnamed: F17.1, SBRIO_AUX.P$1 (POS_AIR)
unnamed: F17.2, Q7.P$1 (C)
unnamed: F18.2, Q8.P$1 (C)
unnamed: Q8.P$2 (B), R12.2
unnamed: F18.1, SBRIO_AUX.P$6 (DIO39)
unnamed: R15.2, U$15.P$2 (B)
unnamed: R12.1, U$15.P$1 (C)
unnamed: R16.2, U$16.P$2 (B)
unnamed: R11.1, U$16.P$1 (C)
unnamed: R5.1, U$17.P$1 (C)
unnamed: R18.2, U$17.P$2 (B)
unnamed: R19.1, U$18.P$1 (C)
unnamed: R6.1, U$18.P$2 (B)
unnamed: Q4.P$2 (B), R20.2
unnamed: R20.1, U$19.P$1 (C)
unnamed: R7.1, U$19.P$2 (B)
unnamed: R21.1, U$20.P$1 (C)
unnamed: R10.1, U$20.P$2 (B)
unnamed: Q9.P$1 (C), R22.1
unnamed: Q9.P$2 (B), R4.2
unnamed: Q13.P$1 (C), R23.1
unnamed: Q13.P$2 (B), R1.2
unnamed: R2.1, U$23.P$1 (C)
unnamed: Q11.P$1 (C), R3.1
unnamed: R24.2, U$23.P$2 (B)
unnamed: Q11.P$2 (B), R25.2
unnamed: Q14.P$2 (B), R26.2
unnamed: Q15.P$2 (B), R28.2
unnamed: R30.1, WHEEL_SPEED.P$2
unnamed: Q17.P$2 (B), R32.2
SHIELD: HV_BOX_CONN.P$2, U$2.P$5 (SHIELD), U$2.P$10 (SHIELD)
STEERING_POS: PEDAL_CONN.P$3, SBRIO_ANALOG.P$21 (AI14), SBRIO_AUX.P$39 (AI14)
THROTTLE_1: PEDAL_CONN.P$1, SBRIO_ANALOG.P$18 (AI5)
THROTTLE_2: PEDAL_CONN.P$2, SBRIO_ANALOG.P$20 (AI6)
VCC: U$3.236 (VCC)

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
